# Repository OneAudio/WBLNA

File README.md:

# WBLNA
Wide Bandwidth low noise amplifier 20Hz-20MHz 20/40dB
-----------------------------------------------------

The WBLNA is a low noise high bandwidth amplifier board.
It can be use to many purpose as noise measurement.

## Specs are :
- 20Hz to 20MHz -3dB bandwidth
- +20dB and +40dB gain individual outputs
- 50 Ohms input/output impedance
- AC or DC coupled input (support +/-20V in AC coupled mode).
- Single 12V@50mA DC input jack
- Low overall cost (~30€ of parts + PCB).

This project  is open source and has been designed using Kicad 5.0.2
The Githu repos include all design files like :
- LTspice simulation files and results
- Schematics
- Bill of materials with Mouser order code
- Picture of prototype
- Pulse mesurements
- Mechanical drawing
- And more...

Frex

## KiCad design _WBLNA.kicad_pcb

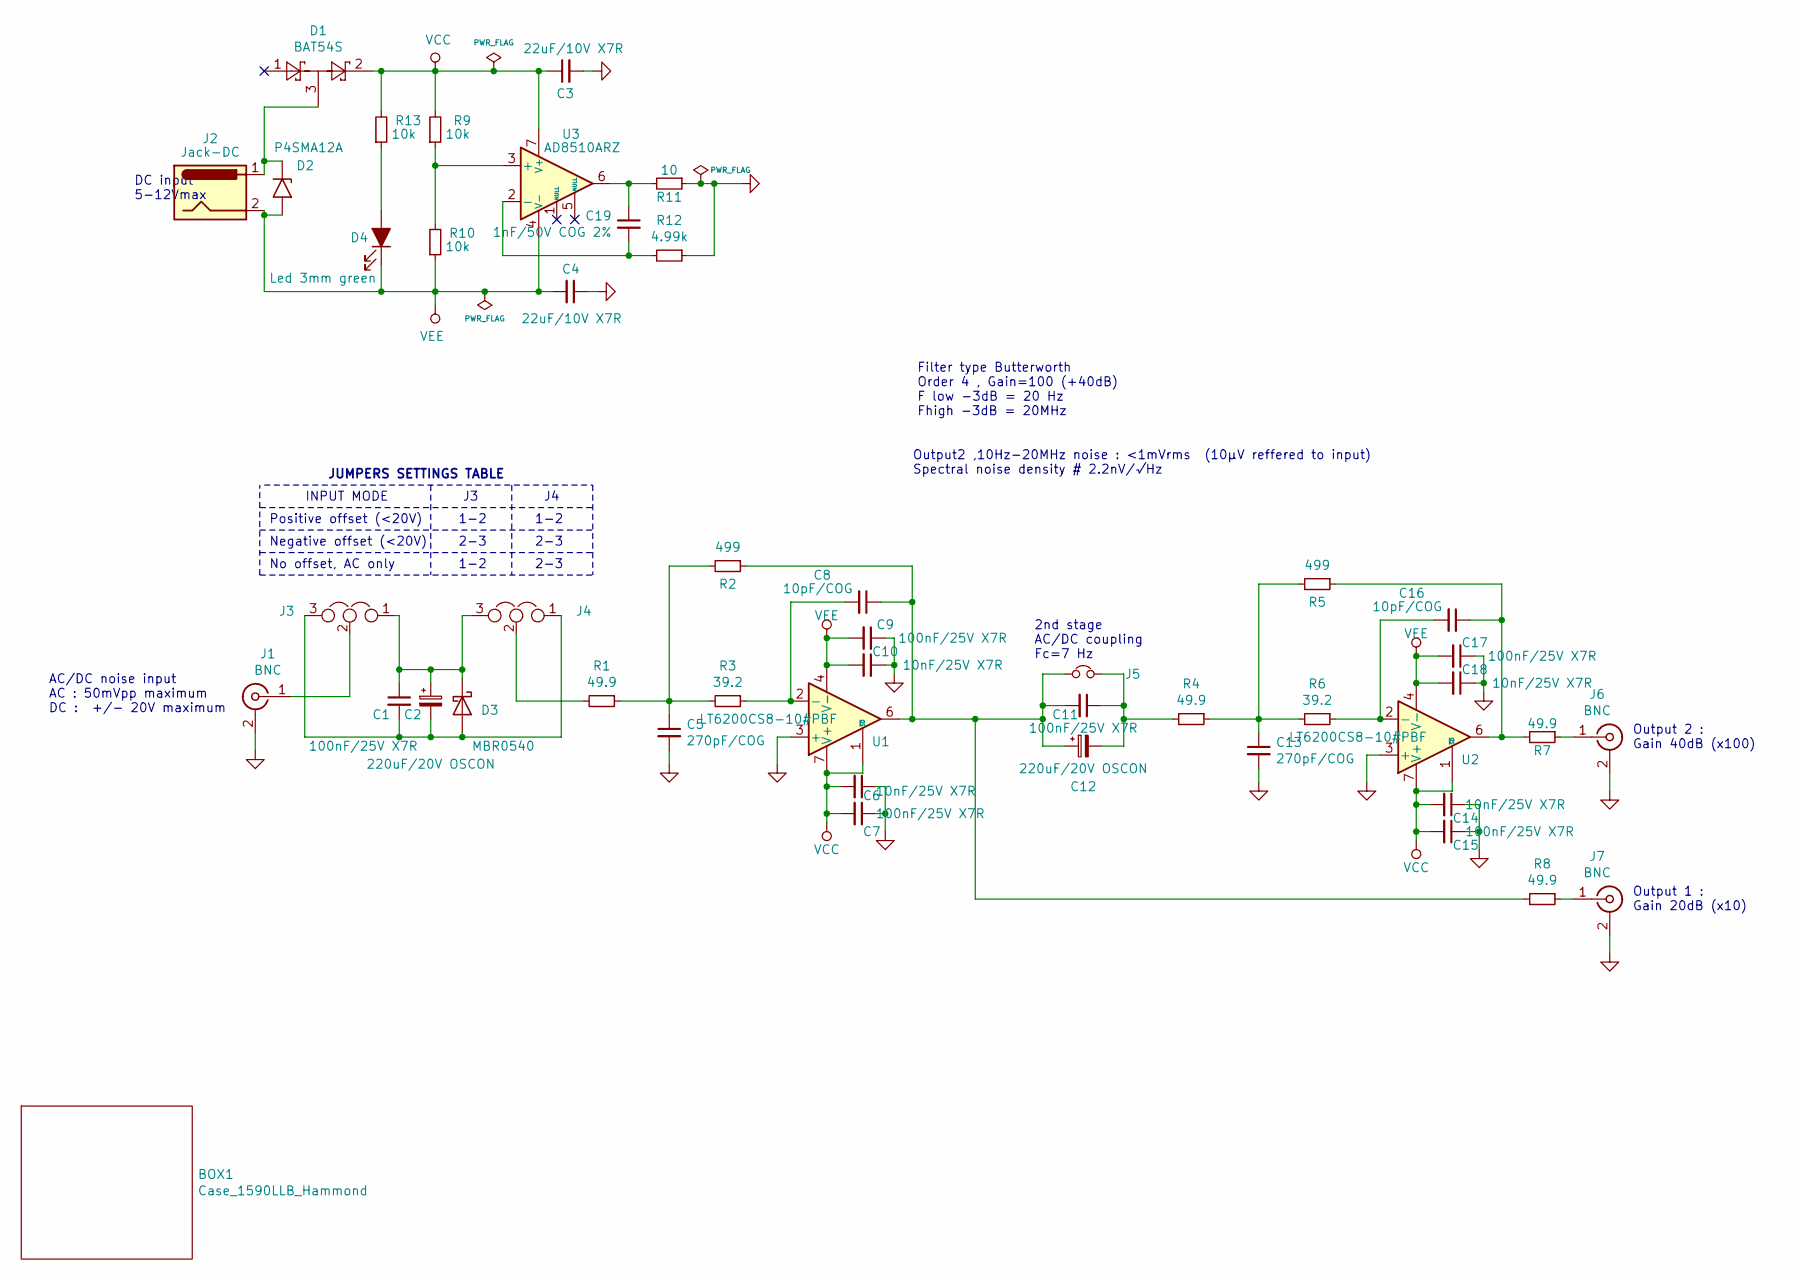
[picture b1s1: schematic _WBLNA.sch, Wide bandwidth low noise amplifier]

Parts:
BOX1: Case_1590LLB_Hammond; 1590LLB
C1: 100nF/25V X7R; C_0805_2012Metric
C2, C12: 220uF/20V OSCON; CP_Elec_8x6.9
C3, C4: 22uF/10V X7R; C_0805_2012Metric
C5, C13: 270pF/COG; C_0805_2012Metric
C6, C10, C14, C18: 10nF/25V X7R; C_0603_1608Metric
C7, C9, C11, C15, C17: 100nF/25V X7R; C_0603_1608Metric
C8, C16: 10pF/COG; C_0805_2012Metric
C19: 1nF/50V COG 2%; C_0805_2012Metric
D1: BAT54S; SOT-23
D2: P4SMA12A; D_SMA
D3: MBR0540; D_SOD-123
D4: Led 3mm green; LED_D3.0mm_Clear
J1, J6, J7: BNC; BNC_edge_solderSMD
J2: Jack-DC; BarrelJackSMD_Wurth_694108106102
J3, J4: Jumper_NC_Dual; PinHeader_1x03_P2.54mm_Vertical
J5: Jumper_NC_Small; PinHeader_1x02_P2.54mm_Vertical
R1, R4, R7, R8: 49.9; R_0805_2012Metric
R2, R5: 499; R_0805_2012Metric
R3, R6: 39.2; R_0805_2012Metric
R9, R10, R13: 10k; R_0805_2012Metric
R11: 10; R_0805_2012Metric
R12: 4.99k; R_0805_2012Metric
U1, U2: LT6200CS8-10#PBF; SOIC-8_3.9x4.9mm_P1.27mm
U3: AD8510ARZ; SOIC-8_3.9x4.9mm_P1.27mm

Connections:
GND: C3.2, C4.1, C5.2, C6.1, C7.1, C9.1, C10.1, C13.2, C14.1, C15.1, C17.1, C18.1, J1.2 (Ext), J6.2 (Ext), J7.2 (Ext), R11.1, R12.1, U1.3 (+), U2.3 (+)
unnamed: C1.1, C2.1, D3.1 (K), J3.1, J4.3
unnamed: C1.2, C2.2, D3.2 (A), J3.3, J4.1
unnamed: C5.1, R1.1, R2.2, R3.2
unnamed: C8.2, R3.1, U1.2 (-)
unnamed: C11.1, C12.2, J5.2, R4.2
unnamed: C8.1, C11.2, C12.1, J5.1, R2.1, R8.2, U1.6
unnamed: C13.1, R4.1, R5.2, R6.2
unnamed: C16.1, R5.1, R7.2, U2.6
unnamed: C16.2, R6.1, U2.2 (-)
unnamed: C19.1, R11.2, U3.6
unnamed: C19.2, R12.2, U3.2 (-)
unnamed: D1.3, D2.1 (K1), J2.1
unnamed: D4.2 (A), R13.1
unnamed: J1.1 (In), J3.2
unnamed: J4.2, R1.2
unnamed: J6.1 (In), R7.1
unnamed: J7.1 (In), R8.1
unnamed: R9.1, R10.2, U3.3 (+)
VCC: C3.1, C6.2, C7.2, C14.2, C15.2, D1.2, R9.2, R13.2, U1.1 (~SD), U1.7 (V+), U2.1 (~SD), U2.7 (V+), U3.7 (V+)
VEE: C4.2, C9.2, C10.2, C17.2, C18.2, D2.2 (A1), D4.1 (K), J2.2, R10.1, U1.4 (V-), U2.4 (V-), U3.4 (V-)

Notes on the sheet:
Output 1 : Gain 20dB (x10)
Output 2 : Gain 40dB (x100)
JUMPERS SETTINGS TABLE
INPUT MODE
Positive offset (<20V)
Negative offset (<20V)
No offset, AC only
1-2
2-3
AC/DC noise input AC : 50mVpp maximum DC : +/- 20V maximum
2nd stage AC/DC coupling Fc=7 Hz
Filter type Butterworth Order 4 , Gain=100 (+40dB) F low -3dB = 20 Hz Fhigh -3dB = 20MHz
Output2 ,10Hz-20MHz noise : <1mVrms (10µV reffered to input) Spectral noise density # 2.2nV/√Hz
DC input 5-12Vmax

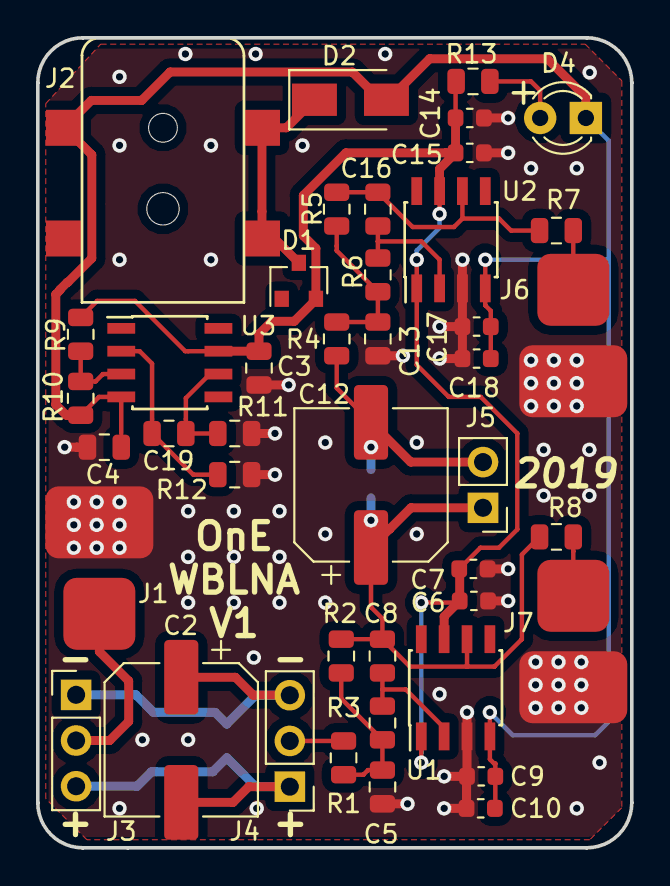
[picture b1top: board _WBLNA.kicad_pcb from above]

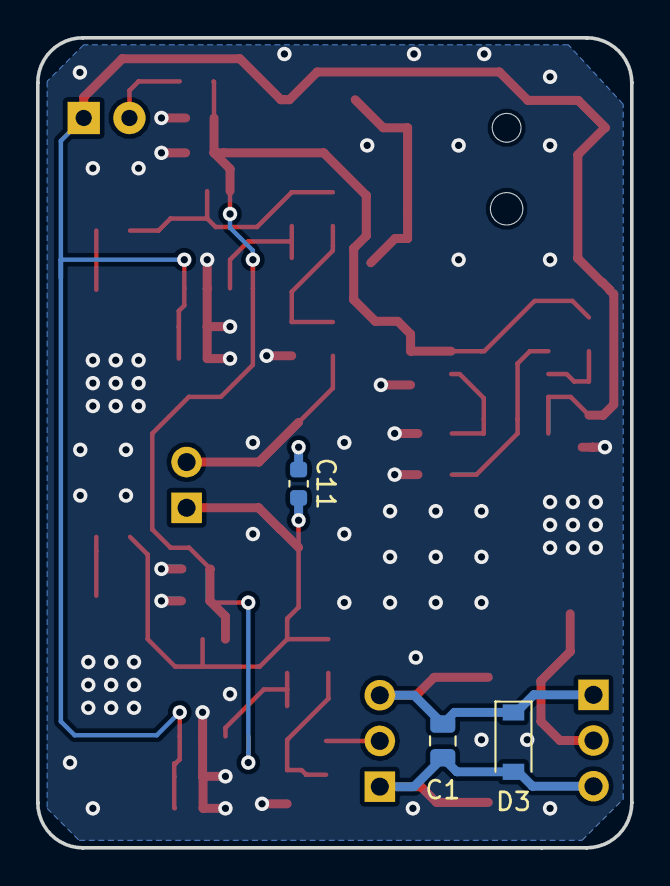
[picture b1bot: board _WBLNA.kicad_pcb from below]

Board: 2 copper layers, 33.0 x 45.0 mm, 47 parts (3 on the bottom side), 21 nets.

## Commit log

2019-10-11 First upload Rev1.0
2019-10-11 Update readme.md file
2019-10-16 Add SND picture
